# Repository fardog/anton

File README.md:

# anton

A quick and dirty air sensor which submits data directly to an [InfluxDB][]
v1 instance, without auth.

I built this because the west coast is on fire, and I ran out of [Luftdaten][]
sensor parts. It's not pretty or full featured but it works.

[InfluxDB]: https://docs.influxdata.com/influxdb/v1.8/
[Luftdaten]: https://sensor.community/

## Requirements

Hardware:

* An ESP development board for ESP8266 or ESP32, such as:
  * NodeMCUv3 or similar ESP8266 platform
  * Lolin32 or similar ESP32 platform
* A particulate sensor, one of:
  * [ZH03B][]
  * [PMS7003][]; Only the PMS7003 has been tested, but other PMSX003 sensors may
    work.
* (Optional) A multisensor:
  * [BME680][] sensor and breakout board; configured for i2c
* (Optional) A CO₂ sensor:
  * [MH-Z19B][]

[ZH03B]: https://www.winsen-sensor.com/sensors/dust-sensor/zh3b.html
[PMS7003]: http://www.plantower.com/en/content/?110.html
[BME680]: https://www.bosch-sensortec.com/products/environmental-sensors/gas-sensors-bme680/
[MH-Z19B]: https://www.winsen-sensor.com/sensors/co2-sensor/mh-z19b.html

Software:

* InfluxDB v1.8

Wire the ZH03B as follows:

* Pin1: `VU`
* Pin2: `Ground`
* ESP8266
  * Pin4: `D4`
  * Pin5: `D3`
* ESP32
  * Pin4: `TX2` (`GPIO17`)
  * Pin5: `RX2` (`GPIO16`)

Or the PMS7003 as follows:

* Pin1: `VU`
* Pin3: `Ground`
* ESP8266
  * Pin7: `D3`
  * Pin9: `D4`
* ESP32
  * Pin7: `TX2` (`GPIO17`)
  * Pin9: `RX2` (`GPIO16`)

(Optional) Wire the BME680 as follows:

* VCC: `3v3`
* GND: `Ground`
* ESP8266
  * SCL: `D1`
  * SDA: `D2`
* ESP32
  * SCL: `SCL` (`GPIO22`)
  * SDA: `SDA` (`GPIO21`)

(Optional) Wire the MH-Z19B as follows, tested only on ESP32:

* VCC: `VU`
* GND: `Ground`
* ESP8266
  * TXD: `D5`
  * RXD: `D6`
* ESP32:
  * TXD: `GPIO18`
  * RXD: `GPIO19`

A 3D printable case for Anton is available at [PrusaPrinters][]. **Note:** the
case fits the ZH03B and ESP8266; for PMS7003 or ESP32, you're on your own right
now, but I'll make one in the future.

[PrusaPrinters]: https://www.prusaprinters.org/prints/40746-case-for-anton-air-quality-influxdb

## Installation

This is built using [PlatformIO][]; refer to their docs on building/uploading.

[PlatformIO]: https://platformio.org/

## Setup

Once uploaded and booted, a wireless network called `anton` will be
created; join this network and you will be directed to a captive portal for
configuration.

## Measurements

Measurements are submitted to the configured database as a measurement named
`particulate_matter`. It will contain the following tags:

* `node` the sensor name
* `location` (optional) the sensor location

…and the following fields containing integer values:

* `p1_0` PM1.0
* `p2_5` PM2.5
* `p10_0` PM10
* `aqi` EPA [AQI][]

[AQI]: https://www.airnow.gov/aqi/aqi-basics/

…and the following string values:

* `aqi_contributor` the primary AQI contributor (highest value); the string will
  match the measurement name, e.g. `p2_5`

**Note:** currently only PM10 and PM2.5 are accounted for in AQI measurements,
following the EPA standard.

**Note:** if the AQI cannot be determined, either due to overflow or other
error, it will be omitted from the InfluxDB submission.

### Multisensor

If you have the optional multisensor connected, the following additional fields
fields will be sent; all are integers unless noted:

* `temperature_c` (float) °C
* `temperature_c_raw` (float) °C, uncompensated
* `humidity` %rh
* `pressure` hPa
* `gas_resistance` Ohm
* `iaq` EPA [IAQ][].
* `iaq_accuracy` IAQ accuracy; see notes
* `co2_equiv` Equivalent CO₂ PPM
* `co2_equiv_accuracy` Equivalent CO₂ accuracy; see notes
* `breath_voc` (float) Breath VOC
* `breath_voc_accuracy` Breath VOC Accuracy; see notes

[IAQ]: https://www.epa.gov/indoor-air-quality-iaq/introduction-indoor-air-quality

**Note:** Various `accuracy` values are provided by the Bosch Sensortec
[BSEC][bsec] library, which have the following meaning ([source][bsec-src]):

* `0` sensor is stabilizing
* `1` readings were too stable to define references
* `2` currently calibrating
* `3` calibrated

[bsec-src]: https://community.bosch-sensortec.com/t5/Question-and-answers/What-does-the-IAQ-accuracy-mean-in-BSEC/qaq-p/5935

### Dedicated CO₂ Sensor

If you have the optional dedicated CO₂ sensor connected, the following
additional integer fields will be sent:

* `co2` PPM

**Note:** when using the optional dedicated CO₂ sensor, you must provide a base
calibration every few weeks. This can be done from the dashboard's calibration
page, and should be initiated when background levels are low. If indoors it's
recommended to open a window and allow good air circulation for several minute
before performing the calibration. This calibration takes 20 minutes.

## Administration

Once configured, a webserver is exposed on port 80 which can be used to view
sensor values, update firmware, change configuration, and reboot or reset the
sensor.

## Changelog

See [CHANGELOG](./CHANGELOG.md).

## Acknowledgements

This was quick to implement due to the following excellent libraries:

* [@ShaggyDog18/SD_ZH03B](https://github.com/ShaggyDog18/SD_ZH03B)
* [@tobiasschuerg/InfluxDB-Client-for-Arduino](https://github.com/tobiasschuerg/InfluxDB-Client-for-Arduino)
* [@prampec/IotWebConf](https://github.com/prampec/IotWebConf)
* [@BoschSensortec/BSEC-Arduino-library][bsec]
* [@fu-hsi/PMS](https://github.com/fu-hsi/PMS)
* [@Erriez/ErriezMHZ19B](https://github.com/Erriez/ErriezMHZ19B)

## License

The code contained in this repo is released under the GNU [GPL-3.0](./LICENSE).

Building this project requires pulling in the various submodules under the `lib`
directory, each of which has their own license; of note the [BSEC][bsec] library
provided by [Bosch Sensortec][bosch] has a closed source binary blob provided
under a unique license which you must abide to use this software.

[bsec]: https://github.com/BoschSensortec/BSEC-Arduino-library
[bosch]: https://www.bosch-sensortec.com/software-tools/software/bsec/

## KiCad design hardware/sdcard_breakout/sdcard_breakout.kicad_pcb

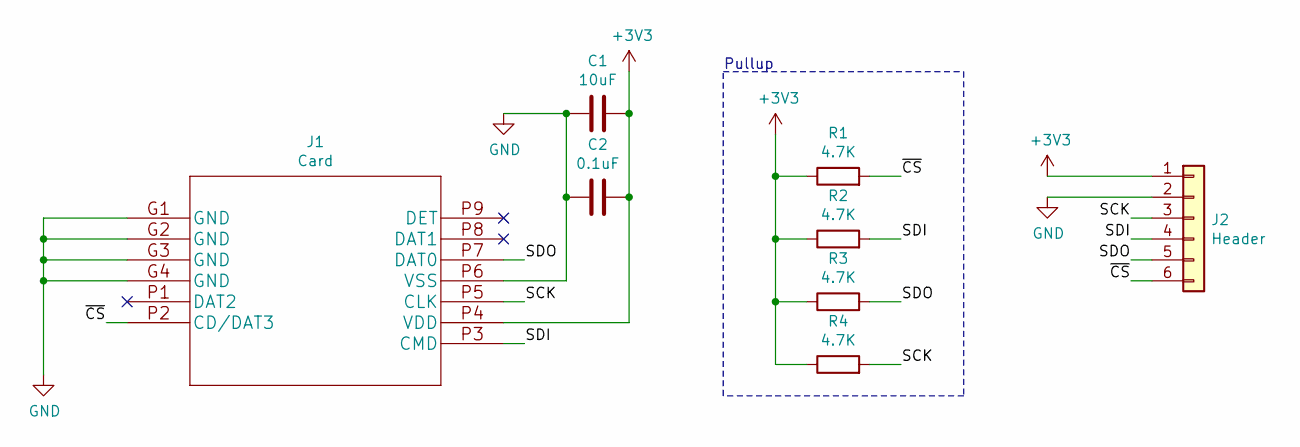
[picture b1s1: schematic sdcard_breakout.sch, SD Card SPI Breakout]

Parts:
C1: 10uF; C_0805_2012Metric
C2: 0.1uF; C_0805_2012Metric
J1: Card; 1051620001
J2: Header; PinHeader_1x06_P2.54mm_Vertical
R1, R2, R3, R4: 4.7K; R_0805_2012Metric

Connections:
+3V3: C1.1, C2.1, J1.P4 (VDD), J2.1, R1.1, R2.1, R3.1, R4.1
/SCK: J1.P5 (CLK), J2.3, R4.2
/SDI: J1.P3 (CMD), J2.4, R2.2
/SDO: J1.P7 (DAT0), J2.5, R3.2
/~CS: J1.P2 (CD/DAT3), J2.6, R1.2
GND: C1.2, C2.2, J1.G1 (GND), J1.G2 (GND), J1.G3 (GND), J1.G4 (GND), J1.P6 (VSS), J2.2

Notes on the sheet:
Pullup

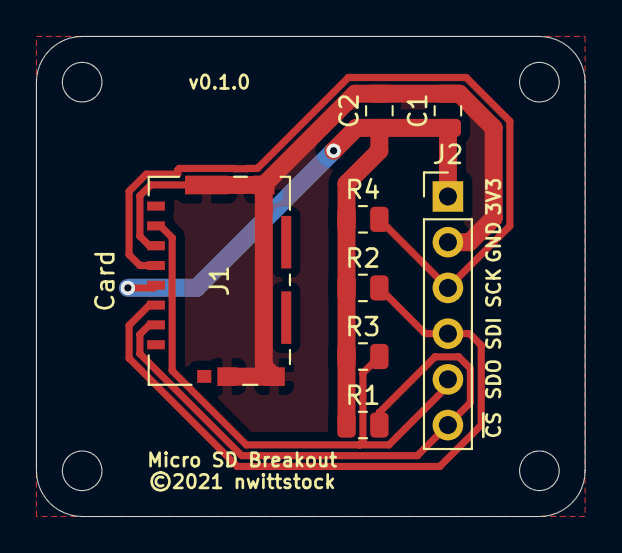
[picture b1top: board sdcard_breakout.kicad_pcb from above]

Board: 2 copper layers, 30.5 x 26.7 mm, 8 parts (0 on the bottom side), 6 nets.

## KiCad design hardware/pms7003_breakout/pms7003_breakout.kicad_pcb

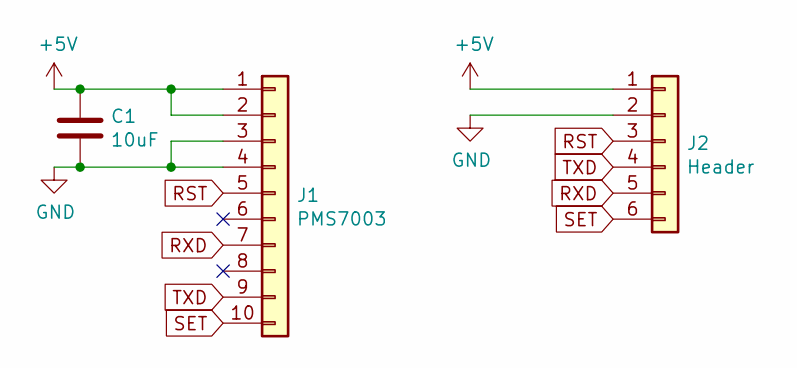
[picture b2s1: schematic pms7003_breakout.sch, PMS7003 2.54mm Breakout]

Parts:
C1: 10uF; C_0805_2012Metric_Pad1.18x1.45mm_HandSolder
J1: PMS7003; PinHeader_2x05_P1.27mm_Vertical
J2: Header; PinHeader_1x06_P2.54mm_Vertical

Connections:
+5V: C1.1, J1.1, J1.2, J2.1
GND: C1.2, J1.3, J1.4, J2.2
RST: J1.5, J2.3
RXD: J1.7, J2.5
SET: J1.10, J2.6
TXD: J1.9, J2.4

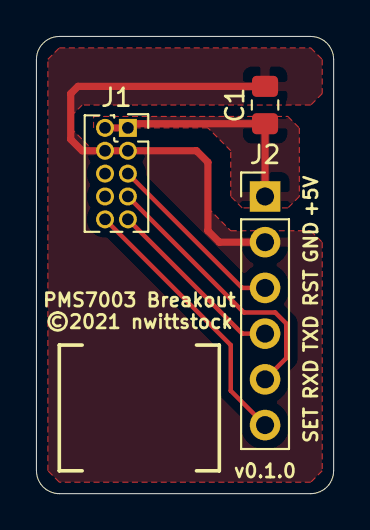
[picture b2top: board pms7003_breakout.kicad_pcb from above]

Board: 2 copper layers, 16.5 x 25.4 mm, 3 parts (0 on the bottom side), 6 nets.

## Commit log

2020-09-13 initital commit
2020-09-14 don't submit failed readings
2020-09-14 use median measurement rather than mean
2020-09-16 reformat, improve logging
2020-09-16 delay before first read, reset on failed sensor wake
2020-09-20 http status page, remote firmware update
2020-09-20 fix order of measurements
2020-09-22 add aqi calculation
2020-09-22 better
2020-09-23 show aqi on index page, submit sample correctly
2020-09-23 public aqi-cpp
2020-09-23 add EPA AQI calculation to reported statistics (#1)
    * add aqi calculation
    * better
    * show aqi on index page, submit sample correctly
    * public aqi-cpp
2020-09-26 improve wifi connection robustness, add location field
2020-09-26 construct measurement string as needed
2020-09-26 support updating config
2020-09-26 Connection, config improvements (#2)
    * improve wifi connection robustness, add location field
    * construct measurement string as needed
    * support updating config
    * update README
2020-10-04 use external influxdb lib
2020-10-04 add note about measurement change
2020-10-04 use external library for influxdb (#3)
    * use external influxdb lib
    * add note about measurement change
2020-10-06 create an abstraction for air sensors
2020-10-06 move into lib directory
2020-10-06 use non-client handling delay within server
2020-10-06 remove extra sleep
2020-10-06 fewer changes
2020-10-06 missed one
2020-10-07 Create sensor abstraction (#4)
    * create an abstraction for air sensors
    * move into lib directory
    * use non-client handling delay within server
    * remove extra sleep
    * fewer changes
    * missed one
2020-10-07 embed git sha into build
2020-10-07 embed git sha into build (#5)
2020-10-08 move sensors out of external lib folder
2020-10-08 use airdata struct for interfaces
2020-10-08 Use AirData struct for interfaces (#6)
    * move sensors out of external lib folder
    * use airdata struct for interfaces
2020-10-08 abstract influxdb reporter
2020-10-10 abstract influxdb reporter (#7)
2020-10-10 move to iotwebconf; first pass, untested
2020-10-12 handle configuration redirect
2020-10-12 add back reset pages
2020-10-18 add bme680 sensor
2020-10-18 make gas temp, millis configurable
2020-10-18 report integer values
2020-10-18 remove altitude utility
2020-10-21 update index page
2020-10-21 add BME680 environment sensor (#9)
    * add bme680 sensor
    * make gas temp, millis configurable
    * report integer values
    * update README
    * remove altitude utility
    * update index page
2020-10-23 fix warnings
2020-10-23 fix warnings (#10)
2020-10-23 move to LittleFS, away from the deprecated SPIFFS
2020-10-25 move to LittleFS, away from the deprecated SPIFFS (#11)
2021-06-18 fix building under latest platformio
2021-07-03 fixes
2021-07-03 fixes, pre-update reorg
2021-07-04 update to latest iotwebconf, new config format
2021-07-04 fixes, working
2021-07-04 rename variables to style
2021-07-04 more renaming
2021-07-04 hard reset, update readme, fix formatting
2021-07-04 support different tx/rx pins
2021-07-04 fix pin comparison, update bme680 lib
2021-07-04 cleanup: pin conversion, fix index page, more utils
    cleanup after the last few direct-to-main commits, which were to
    get things working again on various iterations of sensors I've
    built.
    * allow any pin for serial why not
    * make conversion to pin input better
    * move some things to utils that didn't require global context
2021-07-04 migrate to Iotwebconf from WifiManager (#8)
    * move to iotwebconf; first pass, untested
    * handle configuration redirect
    * add back reset pages
    * fix building under latest platformio
    * fixes
    * fixes, pre-update reorg
2021-07-04 logging fixes
2021-07-04 add pms7003 particulate sensor
2021-07-05 cleanup: pin conversion, fix index page, more utils (#12)
    * cleanup: pin conversion, fix index page, more utils
    cleanup after the last few direct-to-main commits, which were to
    get things working again on various iterations of sensors I've
    built.
    * allow any pin for serial why not
    * make conversion to pin input better
2021-07-05 update readme for merging
2021-07-05 ESP32 support
2021-07-06 add pms7003 particulate sensor (#13)
    * add pms7003 particulate sensor
    * update README
    * update readme for merging
2021-07-07 fix readme
2021-07-07 ESP32 support (#14)
    * ESP32 support
    * fixes
    * fix readme
2021-07-12 fix PMS7003, update README to confirm as working
2021-07-12 fix PMS7003, update README to confirm as working (#15)
2021-08-30 pms7003 breakout board
2021-08-30 remove nested folder
2021-08-30 add version to silkscreen
2021-09-11 Plantower PMS7003 breakout dev board (#16)
    * pms7003 breakout board
    * remove nested folder
    * add version to silkscreen
2021-09-11 micro sd breakout board for development
2021-09-12 add taskscheduler
2021-09-17 wip refactor
2021-09-22 handle all states, retries, timeouts
2021-09-22 remove module that didn't pan out
2021-09-23 remove global variables, fix index page
2021-09-23 fix initialization of Anton class
2021-09-23 add note to README
2021-09-23 Refactor (#17)
    * add taskscheduler
    * wip refactor
    * handle all states, retries, timeouts
    * remove module that didn't pan out
    * remove global variables, fix index page
    * fix initialization of Anton class
2021-09-25 add mhz19b submodule
2021-09-25 prototype co2 sensor
2021-09-25 add lang and charset to pages
2021-09-25 fix calibration confirm route
2021-09-25 require co2 sensor to be enabled; fixed to U0
2021-09-25 hard code pins; web config isn't worth the extra code
2021-09-25 move strings to header
2021-09-25 add co2 to reporter
2021-09-26 don't send failed states
2021-09-26 fix build on esp8266
2021-09-26 rename misc
2021-09-26 subscript
2021-09-26 typo
2021-09-26 CO₂ Sensor, supporting Winsen MH-Z19B (#18)
    * add mhz19b submodule
    * prototype co2 sensor
    * add lang and charset to pages
    * fix calibration confirm route
    * require co2 sensor to be enabled; fixed to U0
    * hard code pins; web config isn't worth the extra code
2021-09-28 increase warm-up time and time between measurements
2021-09-29 fix accidental fallthrough on environment sensor
2021-09-29 apply a fixed offset to BME680 temperature
    this is by no means a complete fix, but how far this value is off
    implies we can't just trust whatever values the sensor returns without
    some calibration/adjustment.
2021-12-05 add editorconfig
2021-12-05 add editorconfig (#19)
2021-12-12 reformat to editorconfig
2021-12-12 reformat to editorconfig (#21)
2021-12-12 use arduino bsec library
2021-12-12 remove unused module
2021-12-12 update modules in README
2021-12-13 update iotwebconf to fix esp8266
2021-12-13 update readme with notes on bsec library
2021-12-13 update README for new fields
2021-12-13 update changelog
2021-12-13 Use Bosch BSEC library for BME680 (#20)
    * use arduino bsec library
    * remove unused module
    * update modules in README
    * update iotwebconf to fix esp8266
    * update readme with notes on bsec library
    * update README for new fields
2021-12-13 update README after renaming primary branch
2021-12-13 fix reported pressure and gas resistances
2022-01-03 report temperature as float; specify temperature offset
2022-01-03 report temperature as float; specify temperature offset (#22)
2022-01-03 show platform on index page
2022-01-03 rename variables
2022-01-03 rename Anton main, create Looper interface
2022-01-03 add timestamp to environmentdata
2022-01-05 refactor web server and network/config concerns
    these various classes are still really interdependent, but at least
    they begin to cordon off a few things in preparation for adding a
    display

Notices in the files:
hardware/pms7003_breakout/pms7003_breakout.kicad_pcb:
©2021 nwittstock
parts and their libraries:
Copyright 2021 Accelerated Designs. All rights reserved.
